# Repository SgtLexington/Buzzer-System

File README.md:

# Buzzer-System
The way that academic competitions work is this: to get points, a player must "buzz in" while or after a question has been answered. Then, the player must answer the question correctly. The moderator will take whoever buzzes in first, so it is very important to practice the buzzing motion to do well. My team has lots of talent, but we are always at a disadvantage when we go to competitions becausewe never practice with the equipment that we use at those competions. Usually at practices, to buzz in, we just hit the desk, while at competions there is a handheld buzzer system where the button to buzz in must be activated by a thumb motion. Naturally, we are slightly outperformed in this category by teams that do practice with a real buzzer system. 
The solution is simple: just buy a buzzer system like the ones at the competitions. 
However, decent quality buzzer systems are expensive. Some of the highest quality systems are $200-$300, and my school simply cannot afford something like that. Given that, I decided to make a buzzer system for us.
Not only does having a buzzer system help the team practice better, but if we bring our own buzzer system to a competition, we get a discount on the entry fee.
Here is the finished system:
[insert pic here]
Prototyping
  Protoboards
  Solidworks
The Main Box:
  Arduino Program
  KiCad and PCB
  Solidworks box & lid
The Team Boxes:
  KiCad and PCB
  Solidworks box & lid
The Buzzers:
  Solidworks MicroUSB & button housings

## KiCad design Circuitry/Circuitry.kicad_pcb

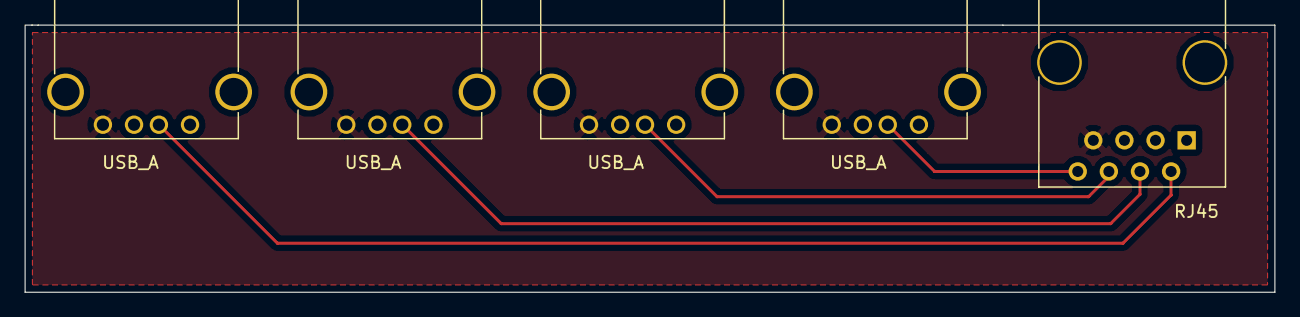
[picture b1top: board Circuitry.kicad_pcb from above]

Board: 2 copper layers, 102.0 x 21.8 mm, 5 parts (0 on the bottom side), 5 nets.

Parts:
Green2: RJ45; RJ45_8
Green-1, Green-2, Green-3, Green-4: USB_A

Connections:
unnamed: Green2.2, Green-1.2
unnamed: Green2.7, Green-1.4, Green-2.4, Green-3.4, Green-4.4
unnamed: Green2.4, Green-2.2
unnamed: Green2.6, Green-3.2
unnamed: Green2.8, Green-4.2

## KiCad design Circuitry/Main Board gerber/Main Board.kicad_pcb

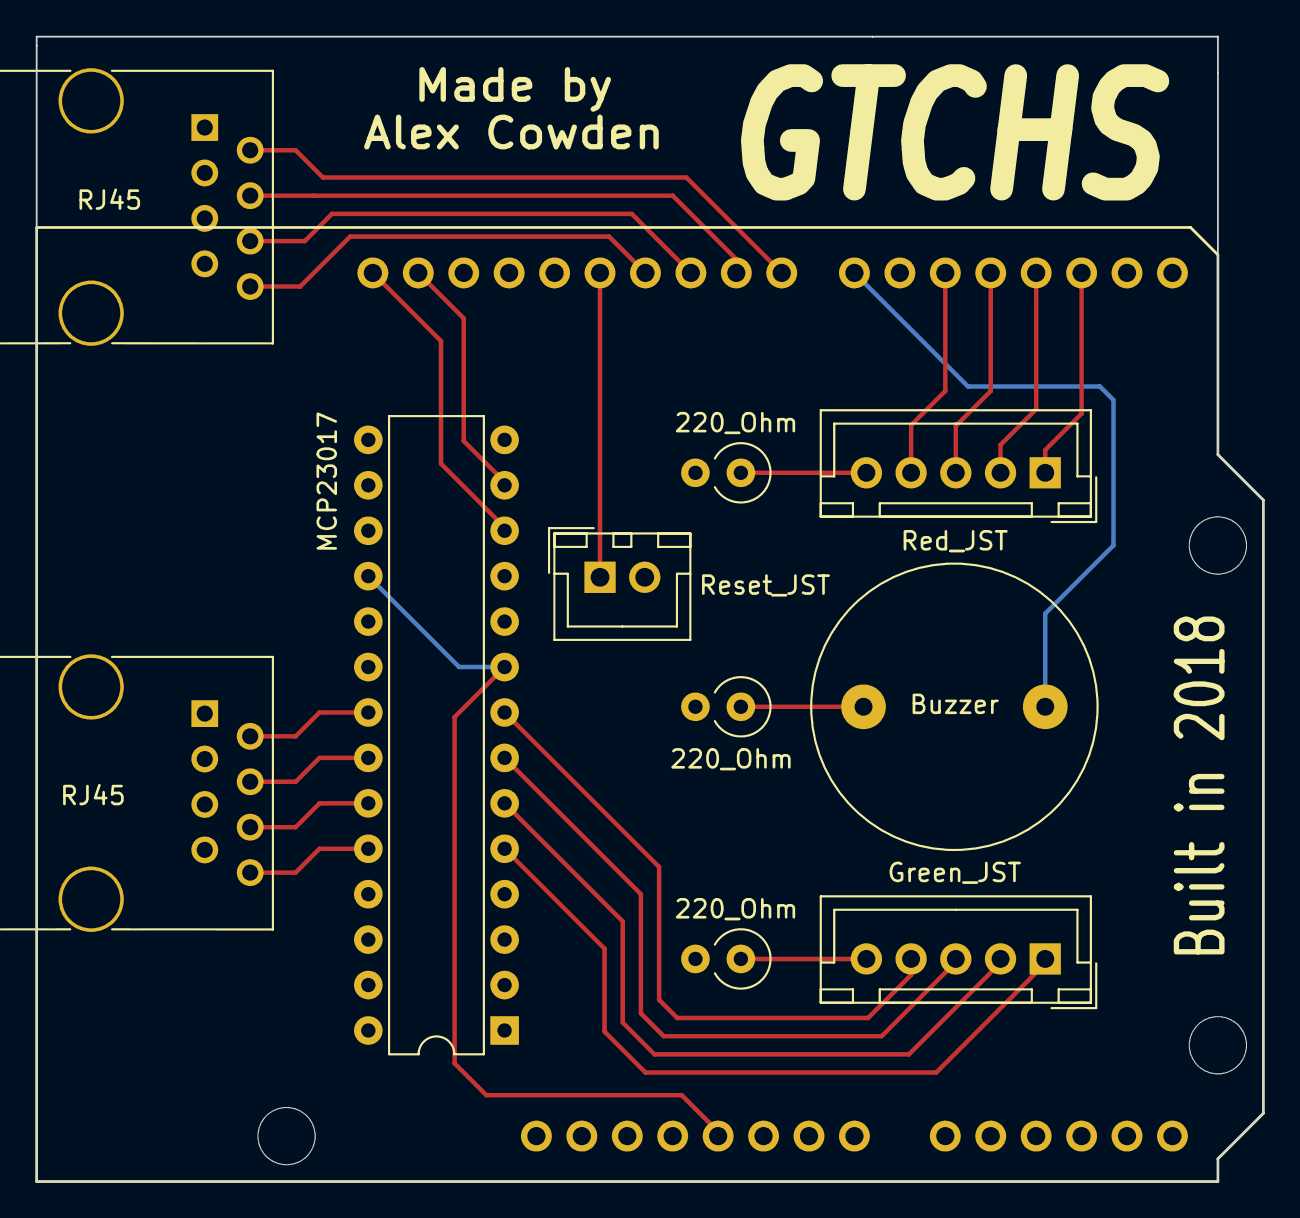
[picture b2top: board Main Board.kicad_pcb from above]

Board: 2 copper layers, 68.6 x 64.0 mm, 11 parts (0 on the bottom side), 25 nets.

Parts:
220_Ohm, 220_Ohm#2, 220_Ohm#3: R; R_Axial_DIN0309_L9.0mm_D3.2mm_P2.54mm_Vertical
ARD1: Arduino_Uno_Shield
Green1: RJ45; RJ45_8
Green_JST: Conn_01x05; JST_XH_B05B-XH-A_05x2.50mm_Straight
IOexpander1: MCP23017; DIP-28_W7.62mm
Red1: RJ45; RJ45_8
Red_JST: Conn_01x05; JST_XH_B05B-XH-A_05x2.50mm_Straight
Reset_JST: Conn_01x02; JST_XH_B02B-XH-A_02x2.50mm_Straight
Sound1: Buzzer; BUZZER

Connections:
BTN_RESET: ARD1.D12, Reset_JST.1
BUZZER: ARD1.D7, Sound1.1
CLOCK: ARD1.SCL, IOexpander1.12
DATA: ARD1.SDA, IOexpander1.13
GND: 220_Ohm.2, 220_Ohm#2.2, 220_Ohm#3.2, ARD1.GND1, ARD1.GND2, ARD1.GND3, Green1.7, IOexpander1.10, IOexpander1.15, IOexpander1.16, IOexpander1.17, Red1.7, Reset_JST.2
G_BTN_1: Green1.2, IOexpander1.21
G_BTN_2: Green1.4, IOexpander1.22
G_BTN_3: Green1.6, IOexpander1.23
G_BTN_4: Green1.8, IOexpander1.24
G_LED_1: Green_JST.1, IOexpander1.5
G_LED_2: Green_JST.2, IOexpander1.6
G_LED_3: Green_JST.3, IOexpander1.7
G_LED_4: Green_JST.4, IOexpander1.8
unnamed: 220_Ohm.1, Red_JST.5
unnamed: 220_Ohm#2.1, Green_JST.5
unnamed: 220_Ohm#3.1, Sound1.2
unnamed: ARD1.5V1, IOexpander1.9, IOexpander1.18
R_BTN_1: ARD1.D8, Red1.2
R_BTN_2: ARD1.D9, Red1.4
R_BTN_3: ARD1.D10, Red1.6
R_BTN_4: ARD1.D11, Red1.8
R_LED_1: ARD1.D2, Red_JST.1
R_LED_2: ARD1.D3, Red_JST.2
R_LED_3: ARD1.D4, Red_JST.3
R_LED_4: ARD1.D5, Red_JST.4

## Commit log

2018-12-19 Initial Version
2018-12-19 Slight update to test
